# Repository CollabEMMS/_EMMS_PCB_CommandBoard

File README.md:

# _EMMS_PCB_CommandBoard
PCB Files for Command Board

<p>Confirmed Latest Version as 2/6/2020

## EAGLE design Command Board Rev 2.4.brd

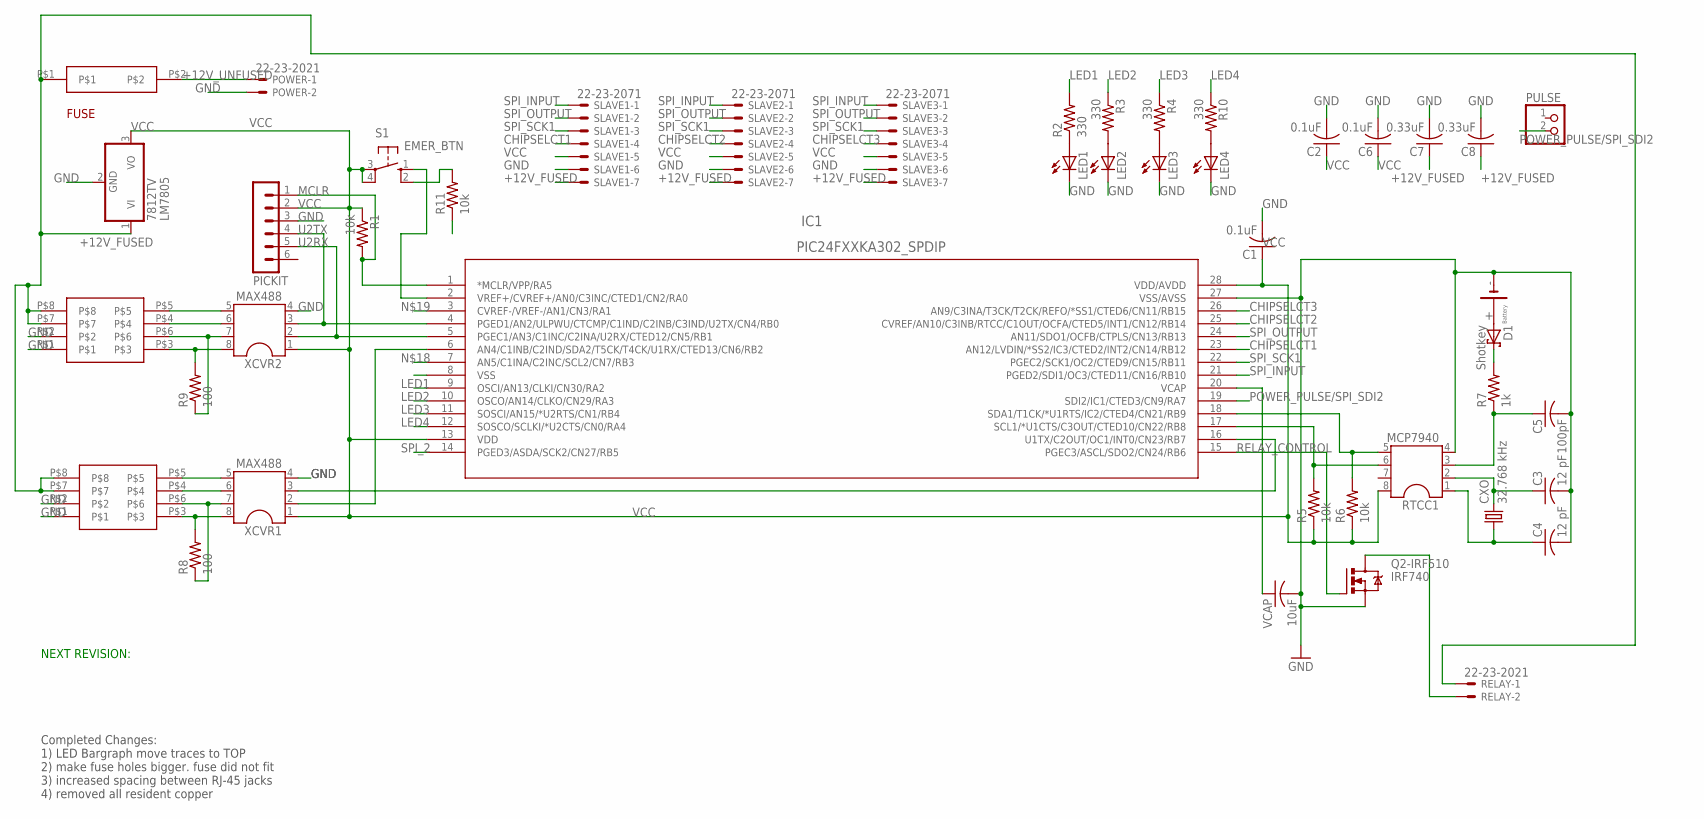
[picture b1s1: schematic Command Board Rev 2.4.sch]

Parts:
BATTERY: BATT_S8211R
C1, C2, C6: 0.1uF; C025-025X050
C3, C4: 12 pF; C025-030X050
C5: 100pF; C075-042X103
C7, C8: 0.33uF; C025-025X050
CXO: 32.768 kHz; TC26V
D1: Shotkey; DO41-7.6
F1: 646_5X20
IC1: PIC24FXXKA302_SPDIP; SPDIP28_300MC
LED1, LED2, LED3, LED4: LED5MM
LM7805: 7812TV; TO220V
PICKIT: MA06-1
POWER: 22-23-2021
PULSE: PINHD-1X2; 1X02
Q2-IRF510: IRF740; TO220BV
R1, R5, R6, R11: 10k; 0207/10
R2, R3, R4, R10: 330; 0207/10
R7: 1k; 0207/10
R8, R9: 100; 0309/12
RELAY: 22-23-2021
RJ1, RJ2: CAT5
RTCC1: MCP7940; DIL08
S1: EMER_BTN; B3F-40XX
SLAVE1, SLAVE2, SLAVE3: 22-23-2071
VCAP: 10uF; C025-050X050
XCVR1, XCVR2: MAX488; DIL08

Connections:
+12V_FUSED: C7.1, C8.1, F1.P$1, LM7805.1 (VI), RELAY.1, RJ1.P$7, RJ1.P$8, RJ2.P$7, RJ2.P$8, SLAVE1.7, SLAVE2.7, SLAVE3.7
+12V_UNFUSED: F1.P$2, POWER.1
CHIPSELCT1: IC1.23 (AN12/LVDIN/*SS2/IC3/CTED2/INT2/CN14/RB12), SLAVE1.4
CHIPSELCT2: IC1.25 (CVREF/AN10/C3INB/RTCC/C1OUT/OCFA/CTED5/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), SLAVE2.4
CHIPSELCT3: IC1.26 (AN9/C3INA/T3CK/T2CK/REFO/*SS1/CTED6/CN1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), SLAVE3.4
EMER_BTN_IN: IC1.2 (VREF+/CVREF+/AN0/C3INC/CTED1/CN2/RA0), S1.1 (S)
GND: BATTERY.P- (-), C1.2, C2.2, C3.2, C4.2, C5.2, C6.2, C7.2, C8.2, IC1.8 (VSS), IC1.27 (VSS/AVSS), LED1.K (C), LED2.K (C), LED3.K (C), LED4.K (C), LM7805.2 (GND), PICKIT.3, POWER.2, Q2-IRF510.S, R11.1, RJ1.P$1, RJ1.P$2, RJ2.P$1, RJ2.P$2, RTCC1.4, SLAVE1.6, SLAVE2.6, SLAVE3.6, VCAP.2, XCVR1.4, XCVR2.4
I2C_SCL1: IC1.17 (SCL1/*U1CTS/C3OUT/CTED10/CN22/RB8), R5.2, RTCC1.6
I2C_SDA1: IC1.18 (SDA1/T1CK/*U1RTS/IC2/CTED4/CN21/RB9), R6.2, RTCC1.5
LED1: IC1.9 (OSCI/AN13/CLKI/CN30/RA2), R2.2
LED2: IC1.10 (OSCO/AN14/CLKO/CN29/RA3), R3.1
LED3: IC1.11 (SOSCI/AN15/*U2RTS/CN1/RB4), R4.1
LED4: IC1.12 (SOSCO/SCLKI/*U2CTS/CN0/RA4), R10.1
MCLR: IC1.1 (*MCLR/VPP/RA5), PICKIT.1, R1.2
unnamed: BATTERY.P1+ (+), BATTERY.P2+ (+), D1.A
unnamed: R11.2, S1.2 (S1)
unnamed: D1.C, R7.2
unnamed: LED1.A, R2.1
unnamed: LED4.A, R10.2
unnamed: LED2.A, R3.2
unnamed: LED3.A, R4.2
POWER_PULSE/SPI_SDI2: IC1.19 (SDI2/IC1/CTED3/CN9/RA7), PULSE.2
RELAY_CONTROL: IC1.15 (PGEC3/ASCL/SDO2/CN24/RB6), Q2-IRF510.G
RELAY_SWITCHED: Q2-IRF510.D, RELAY.2
RTCC_X1: C4.1, CXO.1, RTCC1.1
RTCC_X2: C3.1, CXO.2, RTCC1.2
SPI_2: IC1.14 (PGED3/ASDA/SCK2/CN27/RB5)
SPI_INPUT: IC1.21 (PGED2/SDI1/OC3/CTED11/CN16/RB10), SLAVE1.1, SLAVE2.1, SLAVE3.1
SPI_OUTPUT: IC1.24 (AN11/SDO1/OCFB/CTPLS/CN13/RB13), SLAVE1.2, SLAVE2.2, SLAVE3.2
SPI_SCK1: IC1.22 (PGEC2/SCK1/OC2/CTED9/CN15/RB11), SLAVE1.3, SLAVE2.3, SLAVE3.3
U1RX: IC1.6 (AN4/C1INB/C2IND/SDA2/T5CK/T4CK/U1RX/CTE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), XCVR1.2
U1TX: IC1.16 (U1TX/C2OUT/OC1/INT0/CN23/RB7), XCVR1.3
U1_A: R8.2, RJ2.P$3, XCVR1.8
U1_B: R8.1, RJ2.P$6, XCVR1.7
U1_Y: RJ2.P$5, XCVR1.5
U1_Z: RJ2.P$4, XCVR1.6
U2RX: IC1.5 (PGEC1/AN3/C1INC/C2INA/U2RX/CTED12/CN5/R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), PICKIT.5, XCVR2.2
U2TX: IC1.4 (PGED1/AN2/ULPWU/CTCMP/C1IND/C2INB/C3IND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), PICKIT.4, XCVR2.3
U2_A: R9.2, RJ1.P$3, XCVR2.8
U2_B: R9.1, RJ1.P$6, XCVR2.7
U2_Y: RJ1.P$5, XCVR2.5
U2_Z: RJ1.P$4, XCVR2.6
VBAT_IN: C5.1, R7.1, RTCC1.3
VCAP: IC1.20 (VCAP), VCAP.1
VCC: C1.1, C2.1, C6.1, IC1.13 (VDD), IC1.28 (VDD/AVDD), LM7805.3 (VO), PICKIT.2, R1.1, R5.1, R6.1, RTCC1.8, S1.3, S1.4 (P1), SLAVE1.5, SLAVE2.5, SLAVE3.5, XCVR1.1, XCVR2.1

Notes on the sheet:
NEXT REVISION:
Completed Changes: 1) LED Bargraph move traces to TOP 2) make fuse holes bigger. fuse did not fit 3) increased spacing between RJ-45 jacks 4) removed all resident copper

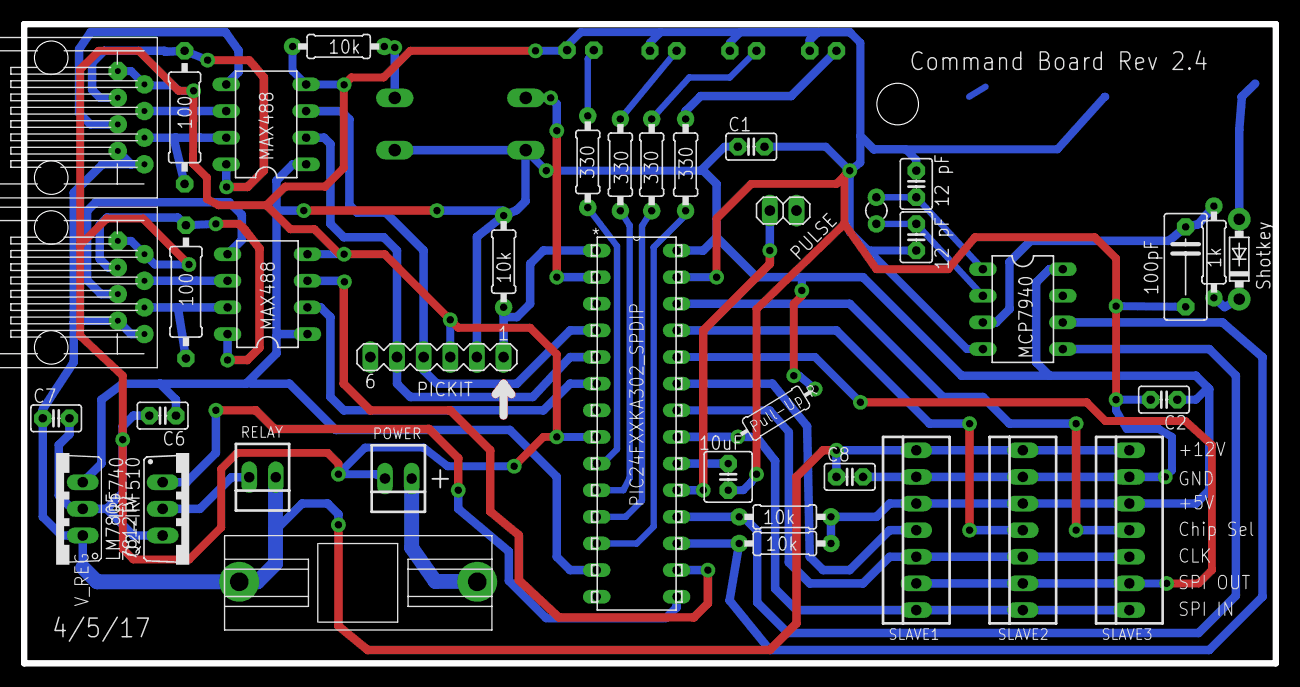
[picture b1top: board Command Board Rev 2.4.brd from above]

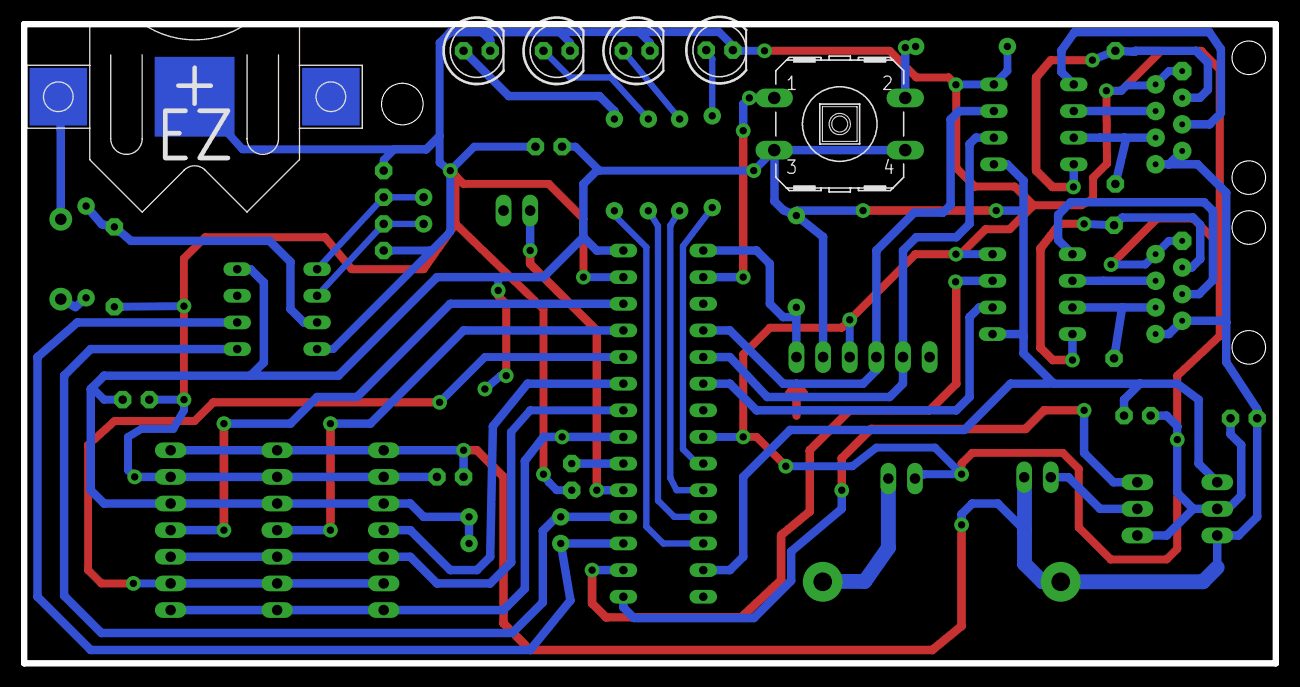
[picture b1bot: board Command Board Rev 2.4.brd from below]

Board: 2 copper layers, 119.4 x 61.0 mm, 45 parts (6 on the bottom side), 44 nets.

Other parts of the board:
U$4: RES_FOOTPRINT

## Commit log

2018-02-06 Init Files
2018-02-20 Init CL
    Added changelog info
2018-02-20 Remove 2.4, Add 2.4.1
    Replaces 2.4 files with 2.4.1
2018-02-20 Updated CL
2018-02-20 Fixed wire
2019-03-05 Fix some design rules and vias
2019-03-07 Command Board PCB revised
2019-03-12 Add button's holes
2019-03-15 Gerbers
2020-02-06 Confirmed the latest version

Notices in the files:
parts and their libraries:
SparkFun-Aesthetics: Licensing: Creative Commons ShareAlike 4.0 International - https://creativecommons.org/licenses/by-sa/4.0
